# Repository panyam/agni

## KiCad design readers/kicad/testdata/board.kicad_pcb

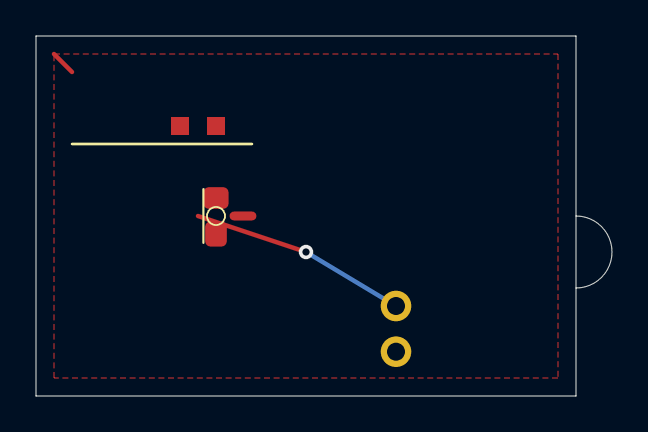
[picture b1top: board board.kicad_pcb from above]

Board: 2 copper layers, 32.0 x 20.0 mm, 3 parts (1 on the bottom side), 2 nets.

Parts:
C?1845: C_0603
J1: CONN; J_1x02
R1: 10k; R_0805

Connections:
GND: C?1845.1, R1.2
SIG: J1.1, R1.1
